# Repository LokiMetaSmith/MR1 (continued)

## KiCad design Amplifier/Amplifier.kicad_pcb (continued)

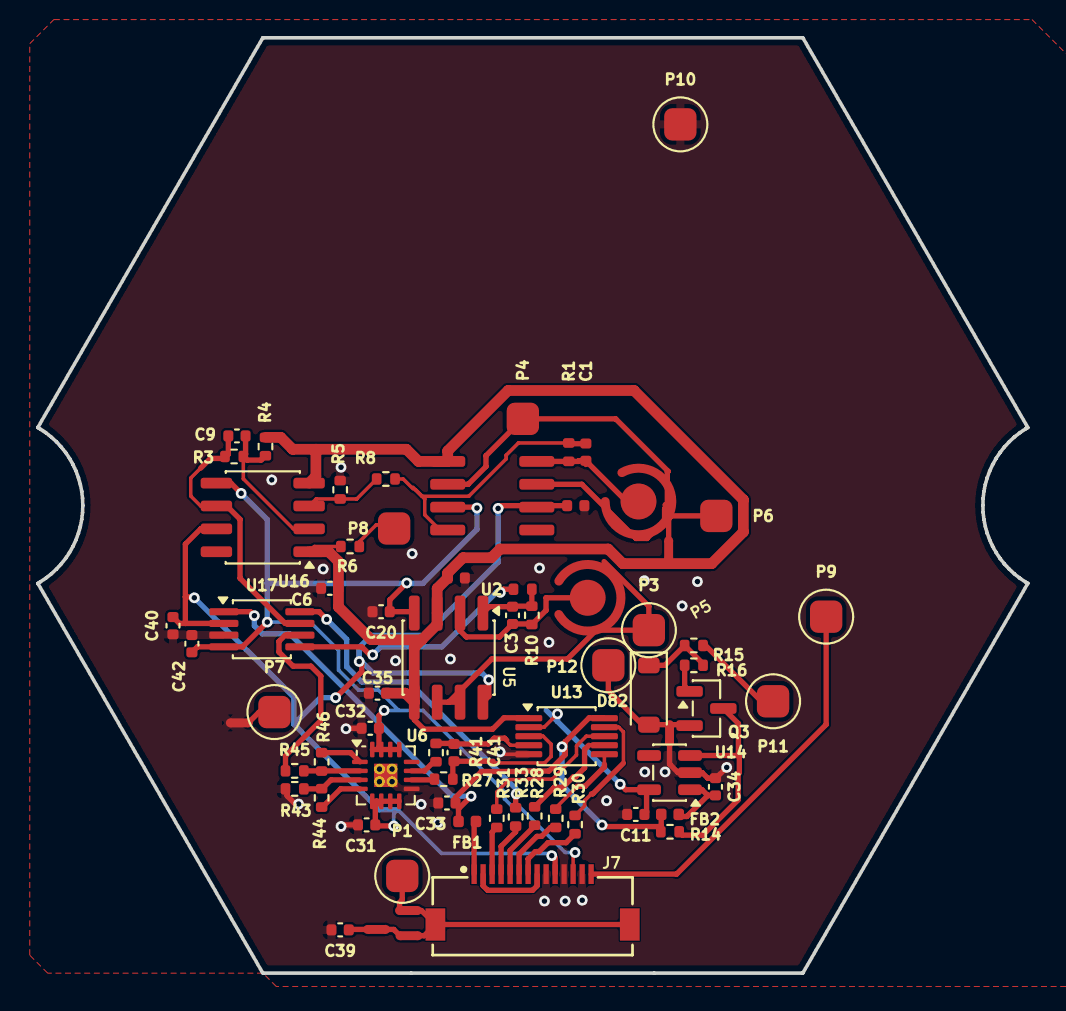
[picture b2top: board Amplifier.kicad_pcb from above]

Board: 2 copper layers, 55.0 x 52.0 mm, 70 parts (1 on the bottom side), 50 nets.

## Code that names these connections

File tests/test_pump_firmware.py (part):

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                if nxt not in visited:
                    visited.add(nxt)
                    queue.append(nxt)
        # Silicon names like PA0, PB6, PC13, etc.
        result.setdefault(
            pname,
            {"pin_nums": [], "labels": found_labels, "no_connect": is_nc},
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
    def test_all_20_assigned_mcu_pins_match_schematic(self):
        expected_fw_to_sch_net = {
            "PIN_PRESS_I2C_SCL": "PRESS_I2C_SCL",
            "PIN_PRESS_I2C_SDA": "PRESS_I2C_SDA",
            "PIN_PD_I2C_SCL": "PD_I2C_SCL",
            "PIN_PD_I2C_SDA": "PD_I2C_SDA",
            "PIN_SBU_I2C_SCL": "SBU_I2C_SCL",
            "PIN_SBU_I2C_SDA": "SBU_I2C_SDA",
            "PIN_PUMP1_STEP": "PUMP1_STEP",
            "PIN_PUMP1_DIR": "PUMP1_DIR",
            "PIN_PUMP2_STEP": "PUMP2_STEP",
            "PIN_PUMP2_DIR": "PUMP2_DIR",
            "PIN_PUMP_UART": "PUMP_UART",
            "PIN_ESTOP_TRIGGER": "ESTOP_TRIGGER_",
            "PIN_MR1_PWR_EN": "MR1_PWR_EN",
            "PIN_USB_SEL_PASS": "USB_SEL_PASS",
            "PIN_PD_ALERT": "PD_ALERT_",
            "PIN_PRESS_ALERT": "PRESS_ALERT_",
            "PIN_LED_FAULT": "LED_FAULT",
            "PIN_LED_PUMP1": "LED_PUMP1",
            "PIN_LED_PUMP2": "LED_PUMP2",
            "PIN_LED_PD_READY": "LED_PD_READY",
            "PIN_LED_MR1_5V": "LED_MR1_5V",
        }
        self.assertEqual(len(expected_fw_to_sch_net), 21)
        self.assertEqual(set(self.direct_pins.keys()), set(expected_fw_to_sch_net.keys()))
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            )

        # Optional PWM and I2C1 aliases resolve consistently
        self.assertEqual(self.alias_pins.get("PIN_PUMP1_PWM"), "PIN_PUMP1_STEP")
        self.assertEqual(self.alias_pins.get("PIN_PUMP2_PWM"), "PIN_PUMP2_STEP")
        self.assertEqual(self.alias_pins.get("PIN_I2C1_SCL"), "PIN_PRESS_I2C_SCL")
        self.assertEqual(self.alias_pins.get("PIN_I2C1_SDA"), "PIN_PRESS_I2C_SDA")

    def test_no_duplicate_or_forbidden_pins(self):
        # Zero duplicate PIN_* macro names in pinout.h
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        self.assertEqual(len(assigned_values), len(set(assigned_values)))

        # Forbidden / no_connect / BOOT0 pins must remain unassigned in pinout.h
        self.assertIn("BOOT0", self.u11_pins["PB8"]["labels"])
        self.assertNotIn("PB8", assigned_values, "BOOT0 pin PB8 assigned in pinout.h")
        nc_pins = [p for p, info in self.u11_pins.items() if info["no_connect"]]
        self.assertGreaterEqual(len(nc_pins), 3)
        for nc_pin in nc_pins:
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
        scl_flags = [f for f in self.build_flags if f.startswith("-DPIN_WIRE_SCL=")]
        sda_flags = [f for f in self.build_flags if f.startswith("-DPIN_WIRE_SDA=")]
        self.assertEqual(scl_flags, ["-DPIN_WIRE_SCL=PA15"])
        self.assertEqual(sda_flags, ["-DPIN_WIRE_SDA=PB9"])
        self.assertEqual(
            scl_flags[0],
            f"-DPIN_WIRE_SCL={self.direct_pins['PIN_PRESS_I2C_SCL']}",
        )
        self.assertEqual(
            sda_flags[0],
            f"-DPIN_WIRE_SDA={self.direct_pins['PIN_PRESS_I2C_SDA']}",
        )

        # 3 completely isolated I2C buses (6 distinct MCU pins)
        press_bus = (self.direct_pins["PIN_PRESS_I2C_SCL"], self.direct_pins["PIN_PRESS_I2C_SDA"])
        pd_bus = (self.direct_pins["PIN_PD_I2C_SCL"], self.direct_pins["PIN_PD_I2C_SDA"])
        sbu_bus = (self.direct_pins["PIN_SBU_I2C_SCL"], self.direct_pins["PIN_SBU_I2C_SDA"])
        all_i2c_pins = list(press_bus + pd_bus + sbu_bus)
        self.assertEqual(len(all_i2c_pins), 6)
        self.assertEqual(len(set(all_i2c_pins)), 6)
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        pd_src = _strip_c_comments(
            (REPO_ROOT / "Pump_firmware" / "src" / "hal" / "stusb4500_pd.cpp").read_text(encoding="utf-8")
        )
        # UCPD dead-battery Rd on PB6 must be disabled before pinMode(PIN_LED_FAULT, ...)
        ucpd_pos = main_src.find("HAL_PWREx_DisableUCPDDeadBattery()")
        pb6_pos = main_src.find("pinMode(PIN_LED_FAULT")
        self.assertNotEqual(ucpd_pos, -1)
        self.assertNotEqual(pb6_pos, -1)
        self.assertLess(ucpd_pos, pb6_pos)

        # Bus constructor / pin assignment contracts
        self.assertRegex(main_src, r"Wire\.setSCL\s*\(\s*PIN_PRESS_I2C_SCL\s*\)")
        self.assertRegex(main_src, r"Wire\.setSDA\s*\(\s*PIN_PRESS_I2C_SDA\s*\)")
        self.assertRegex(main_src, r"SoftI2C\s+pdWire\s*\(\s*PIN_PD_I2C_SDA\s*,\s*PIN_PD_I2C_SCL\b")
        self.assertRegex(main_src, r"TwoWire\s+sbuWire\s*\(\s*PIN_SBU_I2C_SDA\s*,\s*PIN_SBU_I2C_SCL\s*\)")

        # Overvoltage interlock, renegotiation separation, and unconditional 250 ms polling
        self.assertIn("isOvervoltageContract()", main_src)
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#define OUTPUT_OPEN_DRAIN 2

enum MockStmPin : uint8_t {
    PA0 = 0, PA1, PA2, PA3, PA4, PA5, PA6, PA7,
    PA8, PA9, PA10, PA11, PA12, PA13, PA14, PA15,
    PB0, PB1, PB2, PB3, PB4, PB5, PB6, PB7,
    PB8, PB9, PB10, PB11, PB12, PB13, PB14, PB15,
    PC13,
    MOCK_PIN_COUNT
};
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TwoWire Wire;

// -----------------------------------------------------------------------------
// Bit-level STUSB4500QTR Open-Drain I2C Slave Simulator on PB10 (SCL) / PB11 (SDA)
// -----------------------------------------------------------------------------
struct Stusb4500Sim {
    enum State { ST_IDLE, ST_ADDR, ST_REG, ST_WRITE_DATA, ST_READ_DATA };
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void pinMode(uint8_t pin, uint8_t mode) {
    if (pin < MOCK_PIN_COUNT) {
        g_pin_modes[pin] = mode;
        if (pin == PIN_PD_ALERT) {
            g_pin_levels[pin] = HIGH;
        }
    }
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void digitalWrite(uint8_t pin, uint8_t val) {
    if (pin >= MOCK_PIN_COUNT) return;
    g_pin_levels[pin] = val ? HIGH : LOW;
    if (pin == PIN_PD_I2C_SCL) {
        g_pd_sim.master_scl = (val != LOW);
        g_pd_sim.onBusChange();
    } else if (pin == PIN_PD_I2C_SDA) {
        g_pd_sim.master_sda = (val != LOW);
        g_pd_sim.onBusChange();
    }
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
int digitalRead(uint8_t pin) {
    if (pin >= MOCK_PIN_COUNT) return LOW;
    if (pin == PIN_PD_I2C_SCL) return g_pd_sim.master_scl ? HIGH : LOW;
    if (pin == PIN_PD_I2C_SDA) return (g_pd_sim.master_sda && g_pd_sim.slave_sda) ? HIGH : LOW;
    return g_pin_levels[pin];
}

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    memset(g_pin_modes, 0, sizeof(g_pin_modes));
    memset(g_pin_levels, 0, sizeof(g_pin_levels));
    memset(g_analog_vals, 0, sizeof(g_analog_vals));
    g_pin_levels[PIN_PD_ALERT] = HIGH;
    g_pin_levels[PIN_PD_I2C_SCL] = HIGH;
    g_pin_levels[PIN_PD_I2C_SDA] = HIGH;
    g_micros = 1000000ULL;
    g_cis_raw_abp1 = 0x2000;
    g_trans_raw_abp1 = 0x2000;
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    g_pd_sim.resetFactoryNvm(true, 0x20); // Active 15V factory PDO2
    g_pd_sim.nack_soft_reset = true;

    SoftI2C i2c(PIN_PD_I2C_SDA, PIN_PD_I2C_SCL, 100000);
    i2c.begin();
    STUSB4500PD pd(i2c, I2C_ADDR_STUSB4500);

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    assertTrue(pdController.isRdoReadOk(), "RDO read succeeded");
    assertTrue(!g_pd_overvoltage_fault, "Non-PD 5V boot must NOT trip OV fault");
    assertTrue(!g_estop_tripped, "Non-PD 5V boot must NOT trip ESTOP");
    assertTrue(digitalRead(PIN_LED_PD_READY) == LOW, "PD_READY LED LOW without PD contract");

    handleSbuCommand(SbuLink::CMD_RUN_FWD, 100);
    assertTrue(pumpCis.isRunning(), "pumpCis must run on safe 5V non-PD host");
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
    pump_setup();
    assertTrue(!g_pd_overvoltage_fault, "slow PD must not fault in setup");
    assertTrue(digitalRead(PIN_LED_PD_READY) == LOW, "PD_READY LOW while negotiating");

    // Source completes PS_RDY at 250ms -> RDO3 becomes 0x20 (9V)
    g_pd_sim.regs[0x94] = 0x20;
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    assertTrue(!g_pd_overvoltage_fault, "slow PD 9V transition must not fault");
    assertTrue(pdController.isContractActive(), "contract must become active");
    assertTrue(pdController.getVbusVoltageMv() == 9000.0f, "must negotiate 9000 mV");
    assertTrue(digitalRead(PIN_LED_PD_READY) == HIGH, "PD_READY LED must light on 9V");
    return 0;
}

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    assertTrue(g_estop_tripped, "must trigger ESTOP");
    assertTrue(pumpCis.getMode() == DRV8837CMotor::MODE_ESTOP, "pumpCis must be MODE_ESTOP");
    assertTrue(pumpTrans.getMode() == DRV8837CMotor::MODE_ESTOP, "pumpTrans must be MODE_ESTOP");
    assertTrue(digitalRead(PIN_LED_PD_READY) == LOW, "PD_READY LED must be LOW");
    return 0;
}

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    assertTrue(g_estop_tripped, "must trigger ESTOP");
    assertTrue(pumpCis.getMode() == DRV8837CMotor::MODE_ESTOP, "pumpCis MODE_ESTOP");
    assertTrue(pumpTrans.getMode() == DRV8837CMotor::MODE_ESTOP, "pumpTrans MODE_ESTOP");
    assertTrue(digitalRead(PIN_LED_PD_READY) == LOW, "PD_READY LED LOW");
    return 0;
}

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    g_pd_sim.soft_reset_target_rdo3 = 0x20; // Normal 9V boot
    pump_setup();
    assertTrue(!g_pd_overvoltage_fault, "9V boot must succeed");
    assertTrue(digitalRead(PIN_LED_PD_READY) == HIGH, "PD_READY LED HIGH at 9V");

    handleSbuCommand(SbuLink::CMD_RUN_FWD, 100);
    assertTrue(pumpCis.isRunning(), "pumpCis must run before brownout");

    // Silent POR / NVM brownout reset: 0x70=3, 0x94=0x30 (20V), PIN_PD_ALERT stays HIGH
    g_pd_sim.resetFactoryNvm(true, 0x30);
    g_pd_sim.soft_reset_target_rdo3 = 0x30;
    g_pin_levels[PIN_PD_ALERT] = HIGH;

    for (int i = 0; i < 4; ++i) {
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
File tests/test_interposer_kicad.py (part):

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            self.assertIn(f'(symbol "{s}"', sym_txt, f"Symbol {s} must be defined in Interposer.kicad_sym")

        # Validate pin names in PogoPin_Target_12Pin_Distributed
        for pin_name in ["GNDA_SHLD", "WS_CIS_WIDE", "GUARD_WIDE", "GUARD_CIS_A", "WS_CIS", "GUARD_CIS_B", "CE_GNDA", "RE_TRANS", ">PORE_AMP", "GNDA", "WEEP_SENSE", "GNDA_WEEP"]:
            self.assertIn(f'(name "{pin_name}"', sym_txt, f"Pin {pin_name} must be in PogoPin_Target_12Pin_Distributed")

        table_txt = table_file.read_text(encoding="utf-8")
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            nets[m.group(1)] = re.findall(r'\(node\s+\(ref\s+\"([^\"]+)\"\)\s+\(pin\s+\"([^\"]+)\"\)', m.group(0))

        # Route 1: Passive quiet guard for LMP7721 via NT3
        self.assertIn('(label "GUARD"', sch_txt)
        self.assertIn(('NT3', '1'), nets.get('/GUARD', []), "NT3 Pin 1 must connect directly to GUARD net for LMP7721")
        self.assertIn(('NT3', '2'), nets.get('/Vbias', []), "NT3 Pin 2 must connect to Vbias")
        # Route 2: Active guard buffer for GUARD_WIDE using OPA2192 Unit 2
        self.assertIn('(label "GUARD_WIDE"', sch_txt)
        self.assertNotIn('"NT6"', sch_txt, "NT6 must be removed so active GUARD_WIDE is not shorted to Vbias")
        # U16 LTC6268 Gain Stage: R3 feedback restored, R4 tied to Vbias
        self.assertIn(('R3', '1'), nets.get('/Route1_OUT', []), "R3 feedback loop must connect to U16 output (Route1_OUT)")
        self.assertIn(('R3', '2'), nets.get('/Virtual_Ground', []), "R3 pin 2 must connect to Virtual_Ground")
        self.assertIn(('R4', '1'), nets.get('/Vbias', []), "R4 must connect to Vbias")

    def test_amplifier_route2_adg1219_multiplexer_integration(self):
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        # Verify U17 drain connects to Signal_Return (driving R45 differential ADC driver input)
        d_net = [n for n, nodes in nets.items() if ('U17', '6') in nodes]
        self.assertEqual(len(d_net), 1, "U17 pin 6 (D) must belong to exactly one net")
        self.assertEqual(d_net[0], "/Signal_Return", "U17 Drain (pin 6) must connect to Signal_Return")
        self.assertIn(('R45', '1'), nets[d_net[0]], "Signal_Return must feed R45 ADC driver resistor")
        # Ensure U16 (Route 1) and U5 (Route 2) do NOT connect directly to Signal_Return
        self.assertNotIn(('U16', '6'), nets[d_net[0]], "U16.6 must NOT short directly to Signal_Return")
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
        # Verify summing node WS_CIS_WIDE
        wide_net = nets.get("/WS_CIS_WIDE", [])
        self.assertIn(('U5', '2'), wide_net, "U5 pin 2 (-IN) must connect to WS_CIS_WIDE")
        self.assertIn(('R10', '2'), wide_net, "R10 pin 2 must connect to WS_CIS_WIDE")
        self.assertIn(('C3', '2'), wide_net, "C3 pin 2 must connect to WS_CIS_WIDE")
        self.assertIn(('P2', '1'), wide_net, "P2 Pin 1 (WS_CIS_WIDE SMT pin) must connect to WS_CIS_WIDE")

        # Verify control line ROUTE_SEL
        route_net = nets.get("/ROUTE_SEL", [])
        self.assertIn(('U17', '8'), route_net, "U17 IN (pin 8) must connect to /ROUTE_SEL")

        # Verify enable line
        p3v3_net = nets.get("+3V3", [])
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
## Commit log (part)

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2026-01-08 Update Cartridge to Hexagonal Single-Sided PCB stack
    - Updated `PCB_Rigid_Active` to be a full 60mm Hexagonal Plate ("Single-Sided PCBA") with 4 bottom-side electrodes and Top Fluid pass-throughs.
    - Removed `Carrier_Frame_Hex` entirely; the PCB now stacks directly between gaskets.
    - Modified `Gasket_Low_Dead_Volume` to split the bottom layer into Center (Chip) and Trans Loop zones.
    - Implemented "U-Turn" Trans fluid routing in `Plate_1_Base_Hex_3D`:
    - Blind Vias (no bottom puncture) connect Inlet -> Channel -> Up to Pads -> Down to Center.
    - Implemented "Sloped Roof" (Rising Floor) channel geometry under the chip to prevent bubble trapping.
2026-02-01 Update Gasket_Low_Dead_Volume liquid ports to 4mm and deepen cable slot
    - Increased `port_d_laser` from 2.0mm to 4.0mm to match the liquid port size of the rigid plates.
    - Replaced the standard `Cable_Slot_2D` with a custom 12x12mm cutout centered at Y=-25 in `Gasket_Low_Dead_Volume`. This ensures the cable slot cuts deeper into the gasket body (to Y=-19mm) and fully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
    - Updated comments to reflect the new dimensions.
2026-02-19 Fix Housing_Pump_Lid export crash and update mating geometry
    - Replaced complex `threaded_rod` with simple cylinders in `Housing_Pump_Case` to resolve CGAL errors and timeout.
    - Replaced circular O-ring groove sweep with square profile in `Housing_Pump_Lid` to prevent WASM crash.
    - Updated `Housing_Pump_Lid` top feet recesses from trapezoids to 13.5mm cylinders to mate with Reader Case.
    - Increased `Housing_Pump_Lid` bottom indexing lip height to 5mm for better engagement.
2026-02-20 Revert simplifications and fix Pump Lid feet orientation
    - Reverted `Housing_Pump_Case` fluid ports to use `threaded_rod` (previously simplified to cylinders).
    - Reverted `Housing_Pump_Lid` O-ring groove to use `circle` profile (previously simplified to square).
    - Updated `Housing_Pump_Lid` feet recesses to use a tapered `trapezoid` shape (via `linear_extrude(scale=0.8)`) so the recess is wider at the top and narrower at the bottom, matching the mating feet 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
    - Verified that `npm run export` completes successfully (albeit slower) with these complex geometries restored.
